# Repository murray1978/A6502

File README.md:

# A6502
- 6502 project running a modified wozmon and wozaci.
- As it stands ram, rom, 8251 interfaces work, yet to try the 6522 interface, the aci or loading basic from the aci.
- ACI will not work unless you remove the rom, make a daughter board for it with 4K of ram, a connector for the ACI 
  and have the rom selected from address 0xF000h, the ram from 0xE000h, and the ACI at the default 0xC000h as the current
  memory decodes the ROM at 0xE000h.
  
 ## version 2 update.
- 11/10/21 Currently the board uses a modified version of EWoz 1.0 (Not uploaded yet)
- 14/8/21 version 2 is included as /hardware/6502/6502-Controller.pro /hardware/6502/6502-Controller.sch and /hardware/6502/6502-Controller.kicad_pcb.
- Fixed an issue with R2 not having a 5V supply, R2 is part of the reset circuit.
- ~The firmware is 6502mon.asm and 6502aci.asm both have yet to be run.
- ~You may have to play around with the 8251a setup for it to work.
### Backplane 
 - Version 1 of the backplane in progress.

 ## Improvements
 - Any improvements and suggestions are welcome

 ## Errors
  ### For the serial to work
   - Select the 150 jumper for 2400 baud, place a jumper between pin 22 and 24 of the 8251, this connects DTR and DSR.
   - Other baud rates should work

 ## Specs
- 6502 processor at 1Mhz
- 8Kb Ram, IS61C64 start 0x0000
- 8Kb Rom, 28C64 start 0xE000
 One user port via a 6522 at 0xA000
 Serial port via a 8251 at 0x8000, baud rates 2400, 1200, 600, and 300
 
 ## Source
 Current source is for the v2.0 board, 
 
 ### Assembling the source
 Currently I am using asm80.com to assemble the code (downloads as a 64k file ) then a hex editor to trim the last 0x2000 bytes (8k)
 And finaly "burning" the eeprom with the 8k image.

 ## Hardware
 Current board is 6502-Controller.kicad_pcb now version 2

 ### Component Selection
 Mostly 74LS, 74HC support chips, 74HCT may also work.

 ## Issues for 6502.1.1.kicad_pcb
 1.  8251A may require a seperate clock if cpu is at 1mhz and programmed at x64 rate.
 2.  No power light 
 3.  Reset could damage older chips, do not use as is. Replace 100u reset cap with 100n cap.
 4.  8251a reset is active high, not low as shown on board.
 5.  74hc4060 incorrect pinout, leading to misleading baud rate signals.

 ## Changes from 6502.1.1.kicad_pcb to 6502-Controller.kicad_pcb
 - ~Add Clock for 8251A, cannot use procssor clock as the 8251A requires a clock atleast 30 times the baud rate. 
 -  CPU clock works with 8251 ok.
 - ~Add LED Power indicator 
 - [x]  Add/Fix missing silk screen text for, user and expasion ports, U4 etc 
 - [x]  Change pinout for RN1, add a pin. 
 -  ~Redesign baud rate generator? make it smaller? Use x1 or x16 for baud rate selection.~
 - [x]  Move bypass caps for ease of extraction tool access. 
 - ~Change values of Baudrate text, reflect 64x clock speed (see issue 5)~
 - ~Reset, change the basic r/c reset to a 555 or inverter based reset, or 100n cap instead of 100u. 
 - [x]  74hc4060 pin out has to be updated, 

## Future additions

 - Basic, looking at adding a basic ROM at 0xA000, 8Kb https://
 - FDC at 0x23F0 (via isa adapter and 82077 FDC controller)
 - An LCD 2x16 Display or CRT monitor.
 
 ## Version 3 idea's
  - Redesign main board as a edge card including address, data and control bus buffers, retaining Serial I/O
  - Have I/O take up a small chunk of memory, from 0xC000 to 0xE000
  - Backplane with 5V PSU
  - Basic in EPROM, bank switched, monitor code moved down to low memory, (BBC Micro like)

## Code Snippets
### Memory Check/count, from MS Basic

        lda     #<RAMSTART2
        ldy     #>RAMSTART2
        sta     LINNUM
        sty     LINNUM+1
        ldy     #$00
L40D7:
        inc     LINNUM
        bne     L40DD
        inc     LINNUM+1
L40DD:
        lda     #$92 ; 10010010 / 00100100
        sta     (LINNUM),y
        cmp     (LINNUM),y
        bne     L40FA
        asl     a
        sta     (LINNUM),y
        cmp     (LINNUM),y
        beq     L40D7; old: faster
        bne     L40FA
L40EE:
        jsr     CHRGOT
        jsr     LINGET
        tay
        beq     L40FA
        jmp     SYNERR
L40FA:

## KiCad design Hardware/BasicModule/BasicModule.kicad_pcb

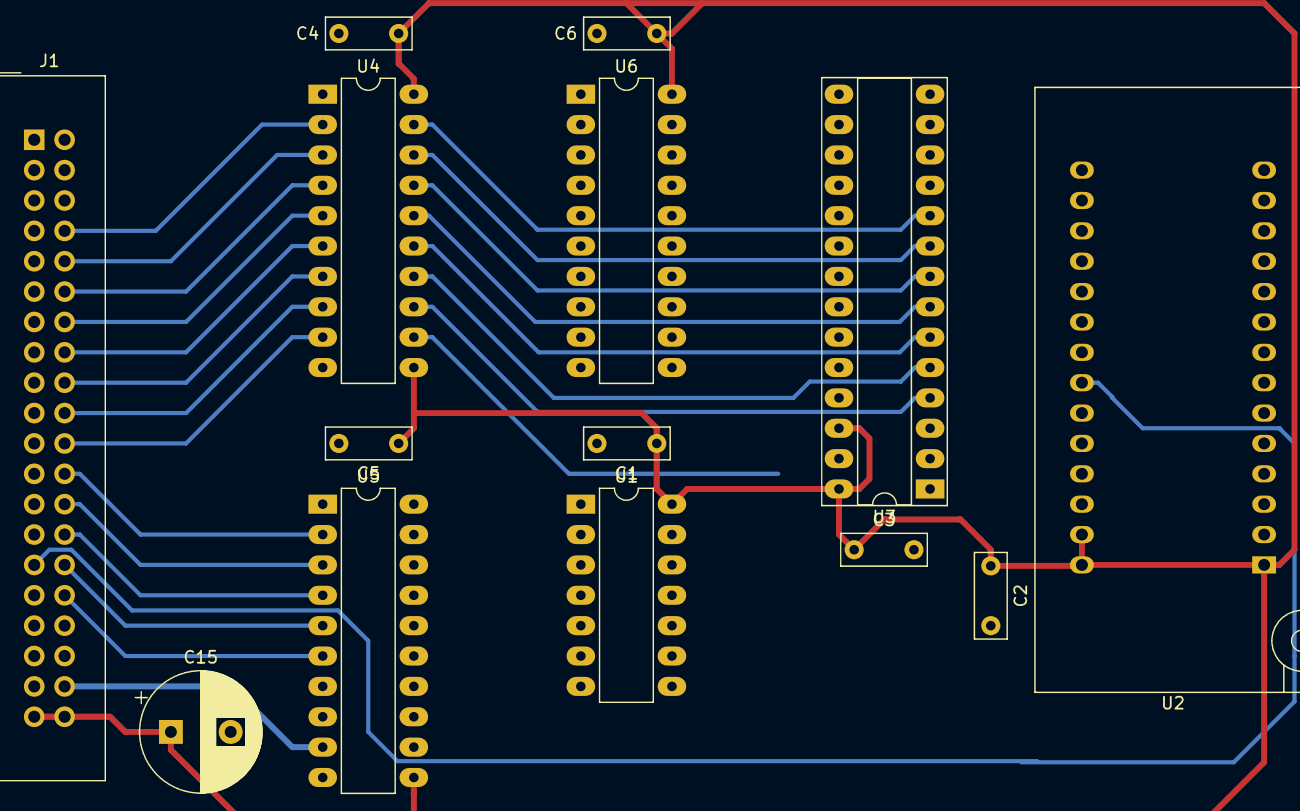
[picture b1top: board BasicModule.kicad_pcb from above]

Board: 2 copper layers, 14 parts (0 on the bottom side), 48 nets.

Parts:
C1, C2, C3, C4, C5, C6: 100n; C_Rect_L7.0mm_W2.5mm_P5.00mm
C15: 10uF; CP_Radial_D10.0mm_P5.00mm
J1: Expanstion Port; IDC-Header_2x20_P2.54mm_Vertical
U1: 74LS04; DIP-14_W7.62mm_LongPads
U2: 2764; DIP_Socket-28_W11.9_W12.7_W15.24_W17.78_W18.5_3M_228-1277-0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
U3: IS61C64; DIP-28_W7.62mm_Socket_LongPads
U4, U5: 74LS573; DIP-20_W7.62mm_LongPads
U6: 74LS245; DIP-20_W7.62mm_LongPads

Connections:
0x2000: J1.35, U3.20
0xC000: J1.29, U2.22
5V: C1.1, C2.1, C3.1, C4.1, C5.1, C6.1, C15.1, J1.39, J1.40, U1.14, U2.1, U2.27, U2.28, U3.26, U3.28, U4.11, U4.20, U5.11, U5.20, U6.20
/A0: U2.10, U3.10, U4.19
/A0_1: J1.8, U4.2
/A1: U2.9, U3.9, U4.18
/A1_1: J1.10, U4.3
/A2: U2.8, U3.8, U4.17
/A2_1: J1.12, U4.4
/A3: U2.7, U3.7, U4.16
/A3_1: J1.14, U4.5
/A4: U2.6, U3.6, U4.15
/A4_1: J1.16, U4.6
/A5: U2.5, U3.5, U4.14
/A5_1: J1.18, U4.7
/A6: U2.4, U3.4, U4.13
/A6_1: J1.20, U4.8
/A7: U2.3, U3.3, U4.12
/A7_1: J1.22, U4.9
/A8: U2.25, U3.25, U5.19
/A8_1: J1.24, U5.2
/A9: U2.24, U3.24, U5.18
/A9_1: J1.26, U5.3
/A10: U2.21, U3.21, U5.17
/A10_1: J1.28, U5.4
/A11: U2.23, U3.23, U5.16
/A11_1: J1.30, U5.5
/A12: U2.2, U3.2, U5.15
/A12_1: J1.32, U5.6
/D0: U2.11, U3.11, U6.18
/D0_1: J1.3, U6.2
/D1: U2.12, U3.12, U6.17
/D1_1: J1.5, U6.3
/D2: U2.13, U3.13, U6.16
/D2_1: J1.7, U6.4
/D3: U2.15, U3.15, U6.15
/D3_1: J1.9, U6.5
/D4: U2.16, U3.16, U6.14
/D4_1: J1.11, U6.6
/D5: U2.17, U3.17, U6.13
/D5_1: J1.13, U6.7
/D6: U2.18, U3.18, U6.12
/D6_1: J1.15, U6.8
/D7: U2.19, U3.19, U6.11
/D7_1: J1.17, U6.9
GND: C1.2, C2.2, C3.2, C4.2, C5.2, C6.2, C15.2, J1.1, J1.2, J1.21, J1.25, J1.37, U1.7, U2.14, U2.20, U3.14, U3.22, U4.1, U4.10, U5.1, U5.10, U6.10, U6.19
R~W: J1.19, U1.5, U3.27
~Read: U1.6, U6.1

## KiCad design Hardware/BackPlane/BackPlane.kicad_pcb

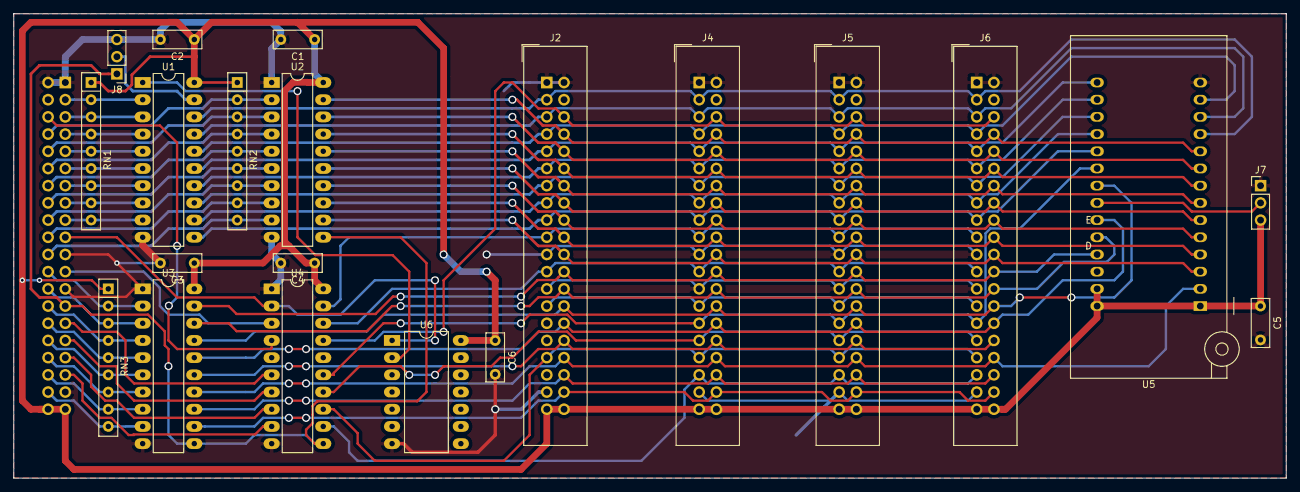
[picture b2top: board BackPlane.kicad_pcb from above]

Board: 2 copper layers, 188.0 x 68.6 mm, 22 parts (1 on the bottom side), 69 nets.

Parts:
C1, C2, C3, C4, C5, C6: 100n; C_Rect_L7.0mm_W2.5mm_P5.00mm
J1: TO A6502; IDC-Header_2x20_P2.54mm_Horizontal
J2: Video; IDC-Header_2x20_P2.54mm_Vertical
J4: FDC; IDC-Header_2x20_P2.54mm_Vertical
J5: EX1; IDC-Header_2x20_P2.54mm_Vertical
J6: EX2; IDC-Header_2x20_P2.54mm_Vertical
J7: User Rom Enable; PinHeader_1x03_P2.54mm_Vertical
J8: DB Enable select; PinHeader_1x03_P2.54mm_Vertical
RN1, RN2, RN3: R_Network08; R_Array_SIP9
U1: 74LS245; DIP-20_W7.62mm_LongPads
U2, U3, U4: 74LS573; DIP-20_W7.62mm_LongPads
U5: 2764; DIP_Socket-28_W11.9_W12.7_W15.24_W17.78_W18.5_3M_228-1277-0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
U6: 74LS04; DIP-14_W10.16mm_LongPads

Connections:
5V: C1.1, C2.1, C3.1, C4.1, C5.1, C6.1, J1.39, J1.40, J2.39, J2.40, J4.39, J4.40, J5.39, J5.40, J6.39, J6.40, J7.3, RN1.1, RN2.1, RN3.1, U1.20, U2.20, U3.20, U4.20, U5.1, U5.27, U5.28, U6.14
/2000: J4.35, J5.35, J6.35, U4.12
/4000: J2.33, J4.33, J5.33, J6.33, U4.13
/6000: J4.31, J5.31, J6.31, U4.14
/A0: J2.8, J4.8, J5.8, J6.8, U2.19, U5.10
/A1: J2.10, J4.10, J5.10, J6.10, U2.18, U5.9
/A2: J2.12, J4.12, J5.12, J6.12, U2.17, U5.8
/A3: J2.14, J4.14, J5.14, J6.14, U2.16, U5.7
/A4: J2.16, J4.16, J5.16, J6.16, U2.15, U5.6
/A5: J2.18, J4.18, J5.18, J6.18, U2.14, U5.5
/A6: J2.20, J4.20, J5.20, J6.20, U2.13, U5.4
/A7: J2.22, J4.22, J5.22, J6.22, U2.12, U5.3
/A8: J2.24, J4.24, J5.24, J6.24, U3.19, U5.25
/A9: J2.26, J4.26, J5.26, J6.26, U3.18, U5.24
/A10: J2.28, J4.28, J5.28, J6.28, U3.17, U5.21
/A11: J2.30, J4.30, J5.30, J6.30, U3.16, U5.23
/A12: J2.32, J4.32, J5.32, J6.32, U3.15
/A13: J2.34, J4.34, J5.34, J6.34, U3.14, U5.2
/A14: J2.36, J4.36, J5.36, J6.36, U3.13
/A15: J2.38, J4.38, J5.38, J6.38, U3.12
/C000: J4.29, J5.29, J6.29, U4.15, U5.20
/CLK: J2.27, J4.27, J5.27, J6.27
/D0: J2.3, J4.3, J5.3, J6.3, U1.18, U5.11
/D1: J2.5, J4.5, J5.5, J6.5, U1.17, U5.12
/D2: J2.7, J4.7, J5.7, J6.7, U1.16, U5.13
/D3: J2.9, J4.9, J5.9, J6.9, U1.15, U5.15
/D4: J2.11, J4.11, J5.11, J6.11, U1.14, U5.16
/D5: J2.13, J4.13, J5.13, J6.13, U1.13, U5.17
/D6: J2.15, J4.15, J5.15, J6.15, U1.12, U5.18
/D7: J2.17, J4.17, J5.17, J6.17, U1.11, U5.19
/RDY: J2.6, J4.6, J5.6, J6.6, U4.17
/R~W: J2.19, J4.19, J5.19, J6.19, U4.19
/_2000: J1.35, U4.9
/_4000: J1.33, U4.8
/_6000: J1.31, U4.7
/_A0: J1.8, RN2.2, U2.2
/_A1: J1.10, RN2.3, U2.3
/_A2: J1.12, RN2.4, U2.4
/_A3: J1.14, RN2.5, U2.5
/_A4: J1.16, RN2.6, U2.6
/_A5: J1.18, RN2.7, U2.7
/_A6: J1.20, RN2.8, U2.8
/_A7: J1.22, RN2.9, U2.9
/_A8: J1.24, RN3.2, U3.2
/_A9: J1.26, RN3.3, U3.3
/_A10: J1.28, RN3.4, U3.4
/_A11: J1.30, RN3.5, U3.5
/_A12: J1.32, RN3.6, U3.6
/_A13: J1.34, RN3.7, U3.7
/_A14: J1.36, RN3.8, U3.8
/_A15: J1.38, RN3.9, U3.9
/_C000: J1.29, U4.6
/_CLK: J1.27, J8.1, U2.11, U3.11, U4.11
/_D0: J1.3, RN1.2, U1.2
/_D1: J1.5, RN1.3, U1.3
/_D2: J1.7, RN1.4, U1.4
/_D3: J1.9, RN1.5, U1.5
/_D4: J1.11, RN1.6, U1.6
/_D5: J1.13, RN1.7, U1.7
/_D6: J1.15, RN1.8, U1.8
/_D7: J1.17, RN1.9, U1.9
/_RDY: J1.6, U4.4
/_R~W: J1.19, U4.2, U6.1
/_~RESET: J1.23, U4.3
/~RESET: J2.23, J4.23, J5.23, J6.23, U4.18
GND: C1.2, C2.2, C3.2, C4.2, C5.2, C6.2, J1.1, J1.2, J1.21, J1.25, J1.37, J2.1, J2.2, J2.21, J2.25, J2.37, J4.1, J4.2, J4.21, J4.25, J4.37, J5.1, J5.2, J5.21, J5.25, J5.37, J6.1, J6.2, J6.21, J6.25, J6.37, J7.1, J8.3, U1.10, U2.1, U2.10, U3.1, U3.10, U4.1, U4.10, U5.14, U6.7
unnamed: J7.2, U5.22
unnamed: J8.2, U1.19
unnamed: U1.1, U6.2

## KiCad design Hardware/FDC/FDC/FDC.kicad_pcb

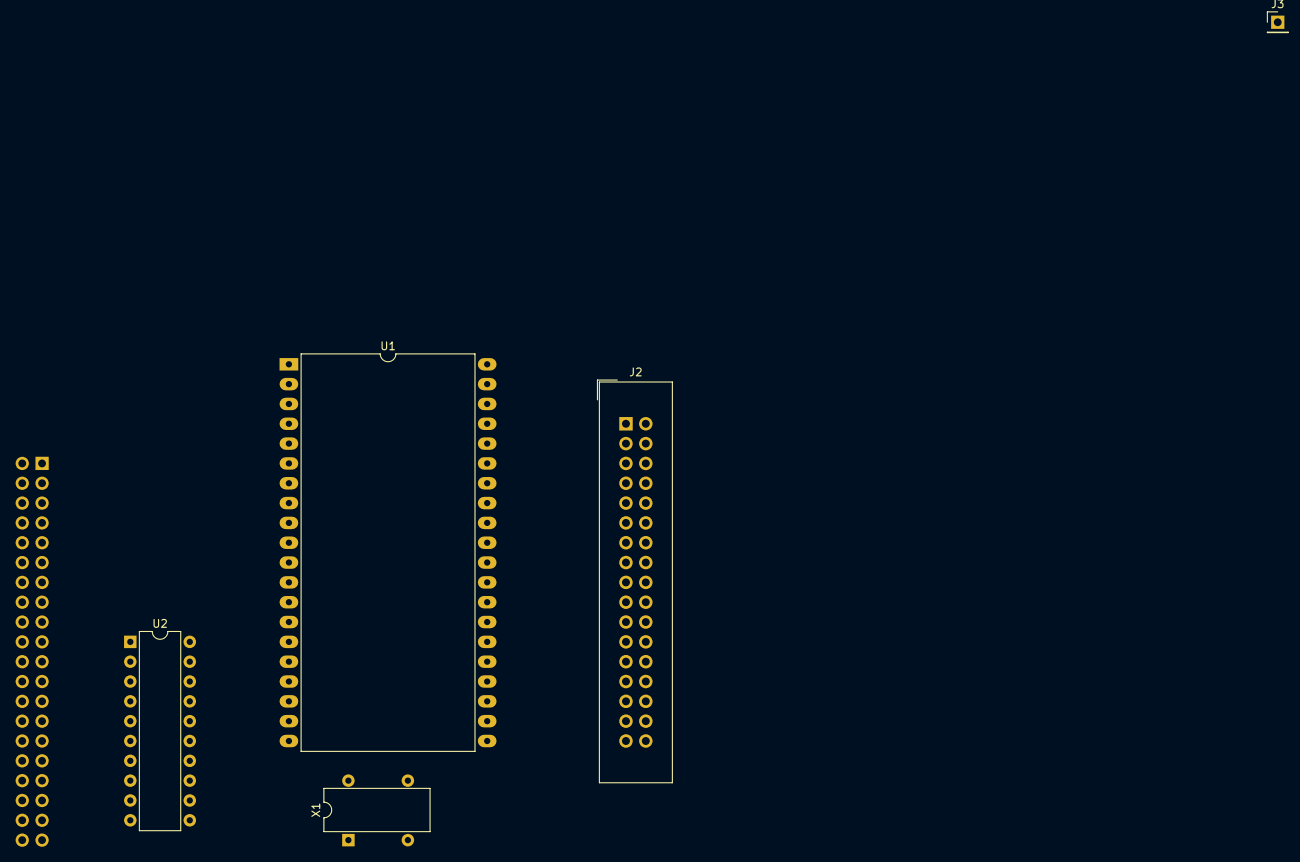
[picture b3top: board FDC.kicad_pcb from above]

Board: 2 copper layers, 6 parts (1 on the bottom side), 41 nets, no tracks yet.

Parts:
J1: FDC_Backplane; PinHeader_2x20_P2.54mm_Horizontal
J2: FDC; IDC-Header_2x17_P2.54mm_Vertical
J3: Conn_01x01; PinHeader_1x01_P2.54mm_Vertical
U1: WD37C65C; DIP-40_W25.4mm_LongPads
U2: GAL16V8; DIP-20_W7.62mm
X1: SG-531; Oscillator_SeikoEpson_SG-8002DC

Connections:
5V: J1.39, J1.40, U1.24, U1.40, U2.20, X1.1, X1.8
/2000: J1.35, U2.5
/A0: J1.8, U2.2
/A1: J1.10, U2.3
/A2: J1.12, U2.4
/CLK: J1.27, U2.1
/D0: J1.3, U1.7
/D1: J1.5, U1.8
/D2: J1.7, U1.9
/D3: J1.9, U1.10
/D4: J1.11, U1.11
/D5: J1.13, U1.12
/D6: J1.15, U1.13
/D7: J1.17, U1.14
/DEN_SEL: J2.2, U1.36
/DSA: J2.14, U1.30
/DSB: J2.12, U1.32
/MOTEA: J2.10, U1.33
/R~W: J1.19, U2.7
/WDATA: J2.22, U1.27
/~DC: J2.34, J3.1
/~DIR: J2.18, U1.28
/~IDX: J2.8, U1.39
/~INT: J1.4, U1.16
/~MOTEB: J2.16, U1.34
/~RDATA: J2.30, U1.20
/~RESET: J1.23, U2.6
/~SIDE: J2.32, U1.25
/~STWP: J2.20, U1.29
/~TR0: J2.26, U1.38
/~WGATE: J2.24, U1.26
/~WP: J2.28, U1.37
GND: J1.1, J1.2, J1.21, J1.25, J1.37, J2.1, J2.3, J2.5, J2.7, J2.9, J2.11, J2.13, J2.15, J2.17, J2.19, J2.21, J2.23, J2.25, J2.27, J2.29, J2.31, J2.33, U1.21, U1.22, U1.31, U2.10, X1.4
unnamed: U1.1, U2.19
unnamed: U1.2, U2.18
unnamed: U1.3, U2.16
unnamed: U1.4, U2.17
unnamed: U1.17, U2.15
unnamed: U1.18, U2.14
unnamed: U1.19, U2.13
unnamed: U1.23, X1.5

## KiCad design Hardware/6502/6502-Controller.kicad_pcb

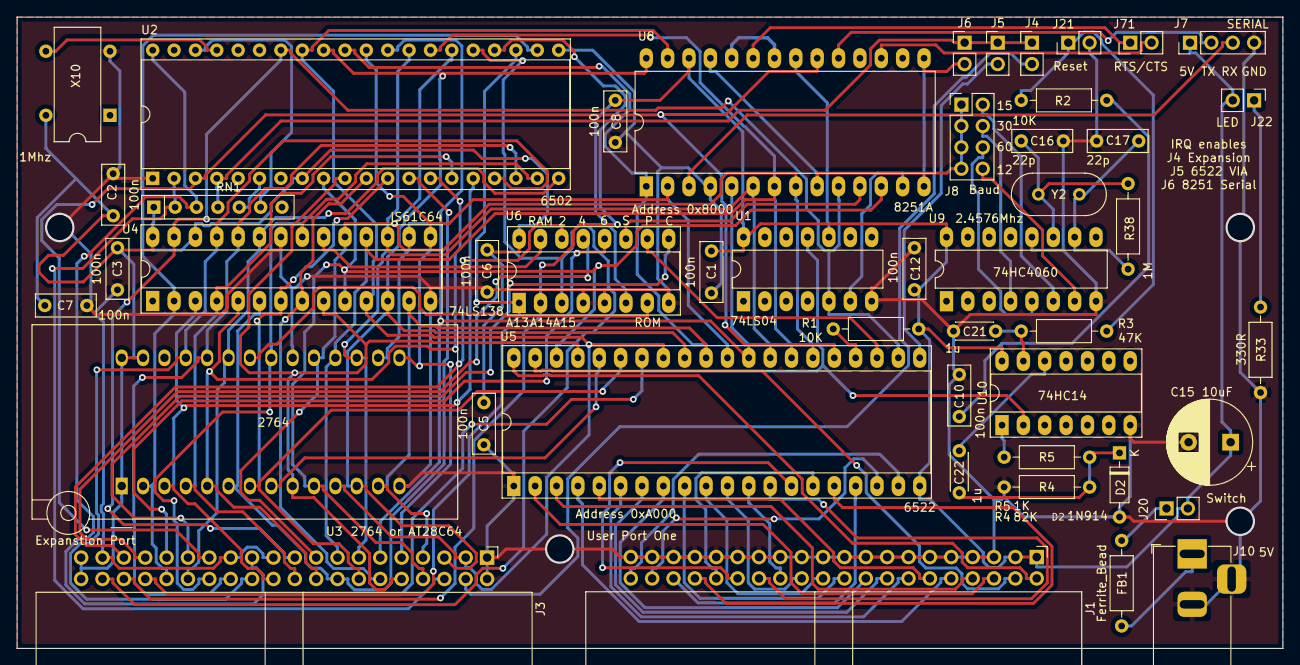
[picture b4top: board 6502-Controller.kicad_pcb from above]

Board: 2 copper layers, 150.5 x 75.1 mm, 47 parts (0 on the bottom side), 87 nets.

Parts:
C1, C2, C3, C5, C6, C7, C8, C10, C12: 100n; C_Rect_L7.0mm_W2.5mm_P5.00mm
C15: 10uF; CP_Radial_D10.0mm_P5.00mm
C16, C17: 22p; C_Rect_L7.0mm_W2.5mm_P5.00mm
C21, C22: 1u; C_Disc_D4.3mm_W1.9mm_P5.00mm
D2: 1N914; D_DO-35_SOD27_P7.62mm_Horizontal
FB1: Ferrite_Bead; R_Axial_DIN0207_L6.3mm_D2.5mm_P10.16mm_Horizontal
J1: User Port One; IDC-Header_2x20_P2.54mm_Horizontal
J3: Expanstion Port; IDC-Header_2x20_P2.54mm_Horizontal
J4: Expansion IRQ Enable; PinHeader_1x02_P2.54mm_Vertical
J5: 6522 IRQ Enable; PinHeader_1x02_P2.54mm_Vertical
J6: SERIAL IRQ Enale; PinHeader_1x02_P2.54mm_Vertical
J7: SERIAL; PinHeader_1x04_P2.54mm_Vertical
J8: Baud; PinHeader_2x04_P2.54mm_Vertical
J10: 5V; BarrelJack_Horizontal
J20: Switch; PinHeader_1x02_P2.54mm_Vertical
J21: Reset; PinHeader_1x02_P2.54mm_Vertical
J22: LED; PinHeader_1x02_P2.54mm_Vertical
J71: RTS/CTS; PinHeader_1x02_P2.54mm_Vertical
R1, R2: 10K; R_Axial_DIN0207_L6.3mm_D2.5mm_P10.16mm_Horizontal
R3: 47K; R_Axial_DIN0207_L6.3mm_D2.5mm_P10.16mm_Horizontal
R4: 82K; R_Axial_DIN0207_L6.3mm_D2.5mm_P10.16mm_Horizontal
R5: 1K; R_Axial_DIN0207_L6.3mm_D2.5mm_P10.16mm_Horizontal
R33: 330R; R_Axial_DIN0207_L6.3mm_D2.5mm_P10.16mm_Horizontal
R38: 1M; R_Axial_DIN0207_L6.3mm_D2.5mm_P10.16mm_Horizontal
RN1: 10K; R_Array_SIP7
U1: 74LS04; DIP-14_W7.62mm_LongPads
U2: 6502; DIP-40_W15.24mm_Socket
U3: 2764; DIP_Socket-28_W11.9_W12.7_W15.24_W17.78_W18.5_3M_228-1277-0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
U4: IS61C64; DIP-28_W7.62mm_Socket_LongPads
U5: 6522; DIP-40_W15.24mm_Socket_LongPads
U6: 74LS138; DIP-16_W7.62mm_Socket_LongPads
U8: 8251A; DIP-28_W15.24mm_LongPads
U9: 74HC4060; DIP-16_W7.62mm_LongPads
U10: 74HC14; DIP-14_W7.62mm_Socket_LongPads
X10: SG-531; Oscillator_SeikoEpson_SG-8002DC
Y2: 2.4576Mhz; Crystal_HC49-U_Vertical

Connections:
0x2000: J3.35, U6.14
0x4000: J3.33, U6.13
0x6000: J3.31, U6.12
0xC000: J3.29, U6.9
5V: C1.1, C2.1, C3.1, C5.1, C6.1, C7.1, C8.1, C10.1, C12.1, C15.1, J1.1, J1.3, J3.39, J3.40, J7.1, J20.2, J22.2, R1.2, R2.1, RN1.1, U1.14, U2.8, U3.1, U3.27, U3.28, U4.26, U4.28, U5.20, U6.6, U6.16, U8.26, U9.16, U10.14, X10.8
/A0: J3.8, U2.9, U3.10, U4.10, U5.38, U8.12
/A1: J3.10, U2.10, U3.9, U4.9, U5.37
/A2: J3.12, U2.11, U3.8, U4.8, U5.36
/A3: J3.14, U2.12, U3.7, U4.7, U5.35
/A4: J3.16, U2.13, U3.6, U4.6
/A5: J3.18, U2.14, U3.5, U4.5
/A6: J3.20, U2.15, U3.4, U4.4
/A7: J3.22, U2.16, U3.3, U4.3
/A8: J3.24, U2.17, U3.25, U4.25
/A9: J3.26, U2.18, U3.24, U4.24
/A10: J3.28, U2.19, U3.21, U4.21
/A11: J3.30, U2.20, U3.23, U4.23
/A12: J3.32, U2.22, U3.2, U4.2
/A13: J3.34, U2.23, U6.1
/A14: J3.36, U2.24, U6.2
/A15: J3.38, U2.25, U6.3
/CA1: J1.2, U5.40
/CA2: J1.4, U5.39
/CB1: J1.38, U5.18
/CB2: J1.40, U5.19
/D0: J3.3, U2.33, U3.11, U4.11, U5.33, U8.27
/D1: J3.5, U2.32, U3.12, U4.12, U5.32, U8.28
/D2: J3.7, U2.31, U3.13, U4.13, U5.31, U8.1
/D3: J3.9, U2.30, U3.15, U4.15, U5.30, U8.2
/D4: J3.11, U2.29, U3.16, U4.16, U5.29, U8.5
/D5: J3.13, U2.28, U3.17, U4.17, U5.28, U8.6
/D6: J3.15, U2.27, U3.18, U4.18, U5.27, U8.7
/D7: J3.17, U2.26, U3.19, U4.19, U5.26, U8.8
/PA0: J1.6, U5.2
/PA1: J1.8, U5.3
/PA2: J1.10, U5.4
/PA3: J1.12, U5.5
/PA4: J1.14, U5.6
/PA5: J1.16, U5.7
/PA6: J1.18, U5.8
/PA7: J1.20, U5.9
/PB0: J1.22, U5.10
/PB1: J1.24, U5.11
/PB2: J1.26, U5.12
/PB3: J1.28, U5.13
/PB4: J1.30, U5.14
/PB5: J1.32, U5.15
/PB6: J1.34, U5.16
/PB7: J1.36, U5.17
B150: J8.2, U9.6
B300: J8.4, U9.4
B600: J8.6, U9.5
B1200: J8.8, U9.7
CLK0: U2.37, X10.5
CLK1: J3.27, U2.3, U5.25, U8.20
GND: C1.2, C2.2, C3.2, C5.2, C6.2, C7.2, C8.2, C10.2, C12.2, C15.2, C16.2, C17.2, C21.2, D2.2, J1.5, J1.7, J1.9, J1.11, J1.13, J1.15, J1.17, J1.19, J1.21, J1.23, J1.25, J1.27, J1.29, J1.31, J1.33, J1.35, J1.37, J1.39, J3.1, J3.2, J3.21, J3.25, J3.37, J7.4, J10.2, J10.3, J21.2, R4.2, R33.1, U1.7, U2.1, U2.21, U3.14, U3.20, U4.14, U4.22, U5.1, U6.4, U6.5, U6.8, U8.4, U9.8, U9.12, U10.7, X10.4
unnamed: C16.1, R38.2, U9.11, Y2.1
unnamed: C17.1, R38.1, U9.10, Y2.2
unnamed: C21.1, R3.2, U10.13
unnamed: C22.1, U10.12
unnamed: C22.2, D2.1, R4.1, R5.1
unnamed: FB1.1, J20.1
unnamed: FB1.2, J10.1
unnamed: J3.4, J4.2
unnamed: J5.2, U5.21
unnamed: J6.2, U8.14, U8.15
unnamed: J7.2, U8.19
unnamed: J7.3, U8.3
unnamed: J8.1, J8.3, J8.5, J8.7, U8.9, U8.25
unnamed: J21.1, R2.2, R3.1
unnamed: J22.1, R33.2
unnamed: J71.1, U8.23
unnamed: J71.2, U8.17
unnamed: R1.1, U5.24
unnamed: R5.2, U10.1
unnamed: RN1.5, U2.6
unnamed: RN1.6, U2.38
unnamed: U1.10, U8.21
RDY: J3.6, RN1.2, U2.2
R~W: J3.19, U1.5, U2.34, U4.27, U5.22, U8.10
~6522_EN: U5.23, U6.10
~8251_EN: U6.11, U8.11
~IRQ: J4.1, J5.1, J6.1, RN1.4, U2.4
~RAM_EN: U4.20, U6.15
~RES: J3.23, RN1.3, U1.11, U2.40, U5.34, U10.2
~ROM_EN: U3.22, U6.7
~Read: U1.6, U8.13

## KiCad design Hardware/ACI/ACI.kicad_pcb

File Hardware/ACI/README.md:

## Current aci issues.
- eprom footprint wrong.
- bypass caps wrong value, use 100n
- 3.5mm sockets to far from edge.
- text on silkscreen a bit hard to read for some values.
- yet to find any more mistakes.

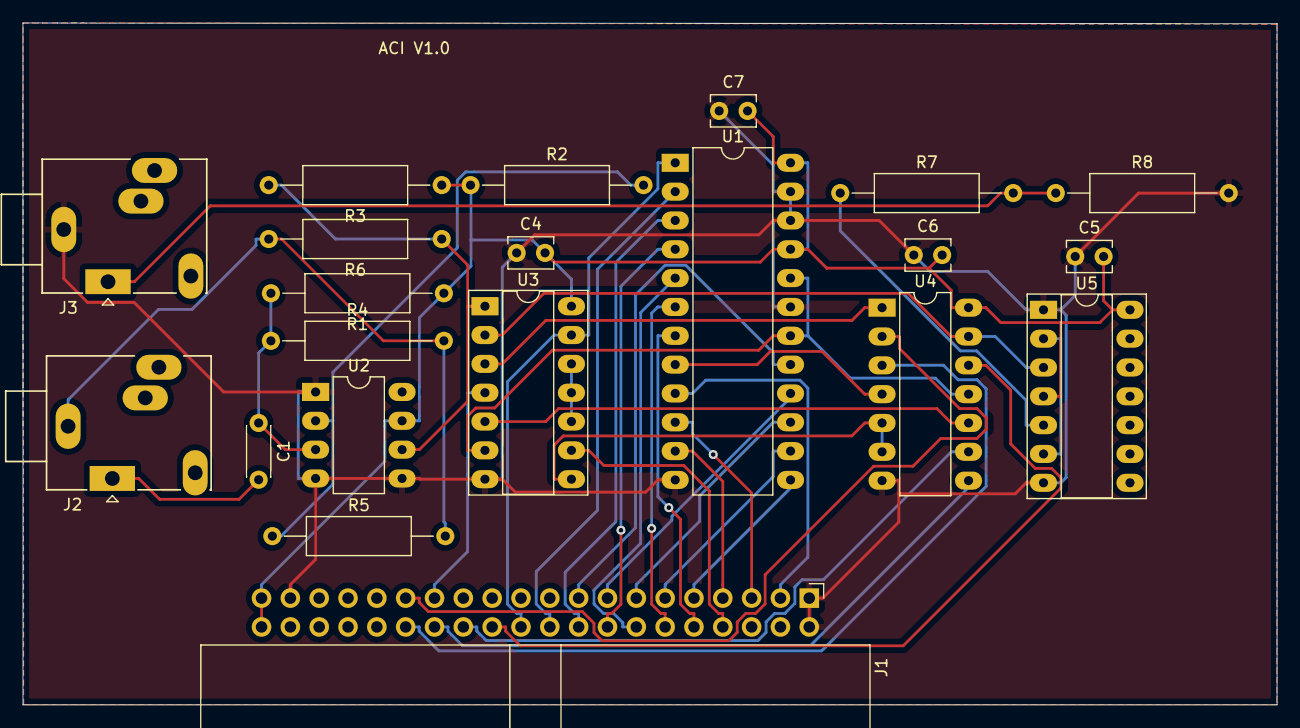
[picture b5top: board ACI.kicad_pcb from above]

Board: 2 copper layers, 110.5 x 60.1 mm, 21 parts (0 on the bottom side), 39 nets.

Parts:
C1: 10n; C_Disc_D4.3mm_W1.9mm_P5.00mm
C4, C5, C6, C7: 10n; C_Disc_D3.8mm_W2.6mm_P2.50mm
J1: SystemBus; IDC-Header_2x20_P2.54mm_Horizontal
J2: From Tape; Jack_3.5mm_Ledino_KB3SPRS_Horizontal
J3: To Tape; Jack_3.5mm_Ledino_KB3SPRS_Horizontal
R1, R2, R4, R5, R7: 10K; R_Axial_DIN0309_L9.0mm_D3.2mm_P15.24mm_Horizontal
R3: 3K; R_Axial_DIN0309_L9.0mm_D3.2mm_P15.24mm_Horizontal
R6: 47K; R_Axial_DIN0309_L9.0mm_D3.2mm_P15.24mm_Horizontal
R8: 10R; R_Axial_DIN0309_L9.0mm_D3.2mm_P15.24mm_Horizontal
U1: AT28C16; DIP-24_W10.16mm_LongPads
U2: LM741; DIP-8_W7.62mm_LongPads
U3: 74LS10; DIP-14_W7.62mm_Socket_LongPads
U4: 74LS02; DIP-14_W7.62mm_LongPads
U5: 74LS74; DIP-14_W7.62mm_Socket_LongPads

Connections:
5V: C4.2, C5.2, C6.2, C7.2, J1.39, J1.40, R1.1, R2.1, R3.1, U1.21, U1.24, U2.7, U3.14, U4.14, U5.4, U5.14
/A1: J1.10, U1.7
/A2: J1.12, U1.6
/A3: J1.14, U1.5
/A4: J1.16, U1.4
/A5: J1.18, U1.3
/A6: J1.20, U1.2
/A7: J1.22, U1.1, U3.13
/A8: J1.24, U4.12
/A9: J1.26, U4.9
/A10: J1.28, U4.8
/A11: J1.30, U4.3
/D0: J1.3, U1.9
/D1: J1.5, U1.10
/D2: J1.7, U1.11
/D3: J1.9, U1.13
/D4: J1.11, U1.14
/D5: J1.13, U1.15
/D6: J1.15, U1.16
/D7: J1.17, U1.17
A0: J1.8, U3.9
A00: U1.8, U4.4
AUDIO_OUT: R3.2, R6.1, U2.6, U3.1
CLK1: J1.27, U3.4
GND: C4.1, C5.1, C6.1, C7.1, J1.1, J1.2, J1.37, J3.S, R8.2, U1.12, U1.19, U1.22, U1.23, U2.1, U2.4, U2.5, U3.7, U4.7, U5.1, U5.7
unnamed: C1.1, R1.2, R4.1, U2.3
unnamed: C1.2, J2.T
unnamed: J2.S, R4.2, R5.2, R6.2
unnamed: J3.T, R7.2, R8.1
unnamed: R2.2, R5.1, U2.2
unnamed: R7.1, U5.5
unnamed: U3.2, U4.13, U5.3
unnamed: U3.3, U4.1
unnamed: U3.5, U4.10
unnamed: U3.8, U4.5, U4.6
unnamed: U3.10, U3.11, U3.12
unnamed: U5.2, U5.6
~4KCS: J1.29, U4.2
~CS: U1.18, U1.20, U3.6, U4.11

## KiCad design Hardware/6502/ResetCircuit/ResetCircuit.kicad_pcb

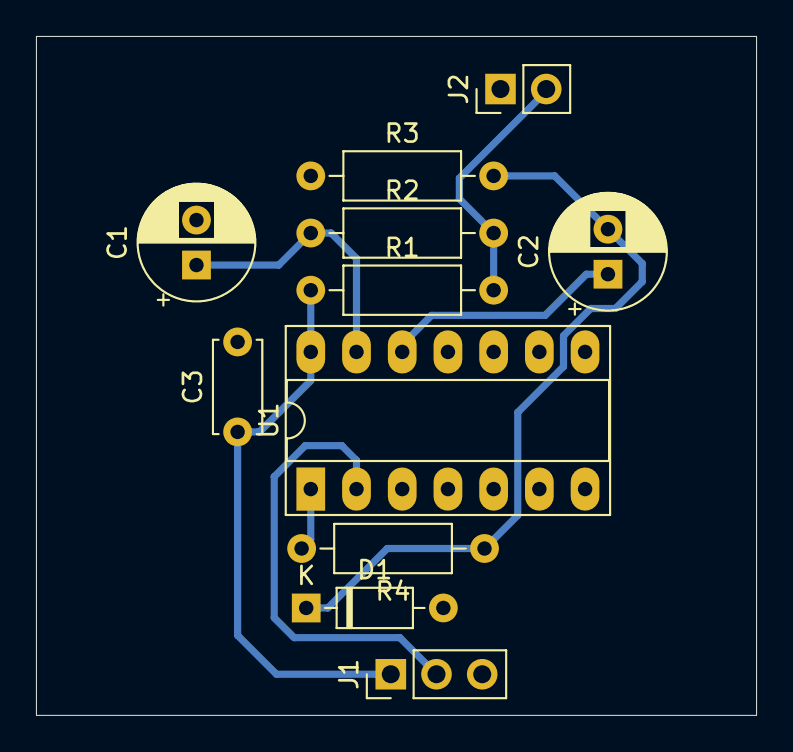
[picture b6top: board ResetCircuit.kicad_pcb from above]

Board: 2 copper layers, 40.0 x 37.7 mm, 11 parts (0 on the bottom side), 8 nets.

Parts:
C1, C2: 1uf; CP_Radial_D6.3mm_P2.50mm
C3: 100n; C_Disc_D5.0mm_W2.5mm_P5.00mm
D1: 1N914; D_DO-35_SOD27_P7.62mm_Horizontal
J1: ~Reset; PinHeader_1x03_P2.54mm_Vertical
J2: Switch; PinHeader_1x02_P2.54mm_Vertical
R1: 10k; R_Axial_DIN0207_L6.3mm_D2.5mm_P10.16mm_Horizontal
R2: 47K; R_Axial_DIN0207_L6.3mm_D2.5mm_P10.16mm_Horizontal
R3: 82K; R_Axial_DIN0207_L6.3mm_D2.5mm_P10.16mm_Horizontal
R4: 1K; R_Axial_DIN0207_L6.3mm_D2.5mm_P10.16mm_Horizontal
U1: 74HC14; DIP-14_W7.62mm_Socket_LongPads

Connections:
/5V: C3.1, J1.1, R1.1, U1.14
/GND: C1.2, C3.2, D1.2, J1.3, J2.1, R3.1, U1.7
unnamed: C1.1, R2.1, U1.13
unnamed: C2.1, U1.12
unnamed: C2.2, D1.1, R3.2, R4.1
unnamed: J1.2, U1.2
unnamed: J2.2, R1.2, R2.2
unnamed: R4.2, U1.1

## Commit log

2021-05-18 Update readme
    Added comments about 8251a and reset cap.
2021-05-19 Update of readme
2021-05-20 Update of project
2021-05-22 Update of PCB
    Updating PCB to newest version, fixing no power light, reset circuit, 8251a reset addition and incorrect 74HC4060 pin out corrections.
    Changed address of 8251a from 0xC000 to 0x8000 on PCB.
2021-05-22 Update README.md
    Update of read me to reflect changes to PCB and Schematic.
2021-05-22 Added current version of the monitor
2021-05-22 Update 6502mon.asm, Added 6502mon.bin
    Updated 6502mon.asm and added 6502mon.bin
2021-05-22 Update 6502.mon
    Added 6502aci.asm
2021-06-06 6502 project update
    Added Gerber's, PCB and updated schematic with single step (not on PCB)
2021-06-14 Created readme
2021-08-14 Fixed R2 issue
    Fixed issue with R2 not having a connection to 5V rail
2021-08-14 Update 6502mon.asm
    Changed 8521a uart initalisation, 1x frequency not 64x frequency
2021-08-14 Version 2 silkscreen
    Update of silkscreen to indicate version2
2021-08-26 Update
    Added Backplane schematics, not suitable for production yet.
    Added Comments in controller schematic for memory mappings.
    FDC and Graphics options on the cards.
2021-09-05 Update For 6502 Controller
    Added Notes to Schematic for Baud rate Generator.
    Added source for New Kernel
    Changed 6502monV1.1.asm baud rate clock to x1 (should be x64)
2021-09-05 Update 6502mon.asm
    Change to x64 rate
2021-09-05 Update README.md
    Added Serial usage notes
2021-09-05 update
    Working? wozmon.a65.bin added
2021-09-07 Update
    Working to get Serial up
2022-09-30 Update README.md
    Added Hardware error note
2022-09-30 Update 6502mon.asm
    13 months of trying to solve an issue, down to "1 line", to put it politely
2022-09-30 Update
    Update of Projects
2022-09-30 Update
    Added FDC prototypes and VIA test code
2022-10-01 Update
    Back plane - adding inverters and control signal buffers to schematic, working on pcb for back plane.
    6502.mon - added revised memory locations for devices
2022-10-01 Update
    Laying out tracks
2022-10-12 Update
    Added monEXT.asm ( use this one for A6502 board )
2022-10-25 update
    Changed 74LS373 to 74LS573, added pull up resistors to input lines
2022-10-25 Update fp-info-cache
2022-11-03 update added basic module
    issue with 74LS245, unit need's to be selected when the ROM and RAM are selected during clock 2.
2022-11-04 Update README.md
    Added a code snippet for Memory Checking from MS Basic
